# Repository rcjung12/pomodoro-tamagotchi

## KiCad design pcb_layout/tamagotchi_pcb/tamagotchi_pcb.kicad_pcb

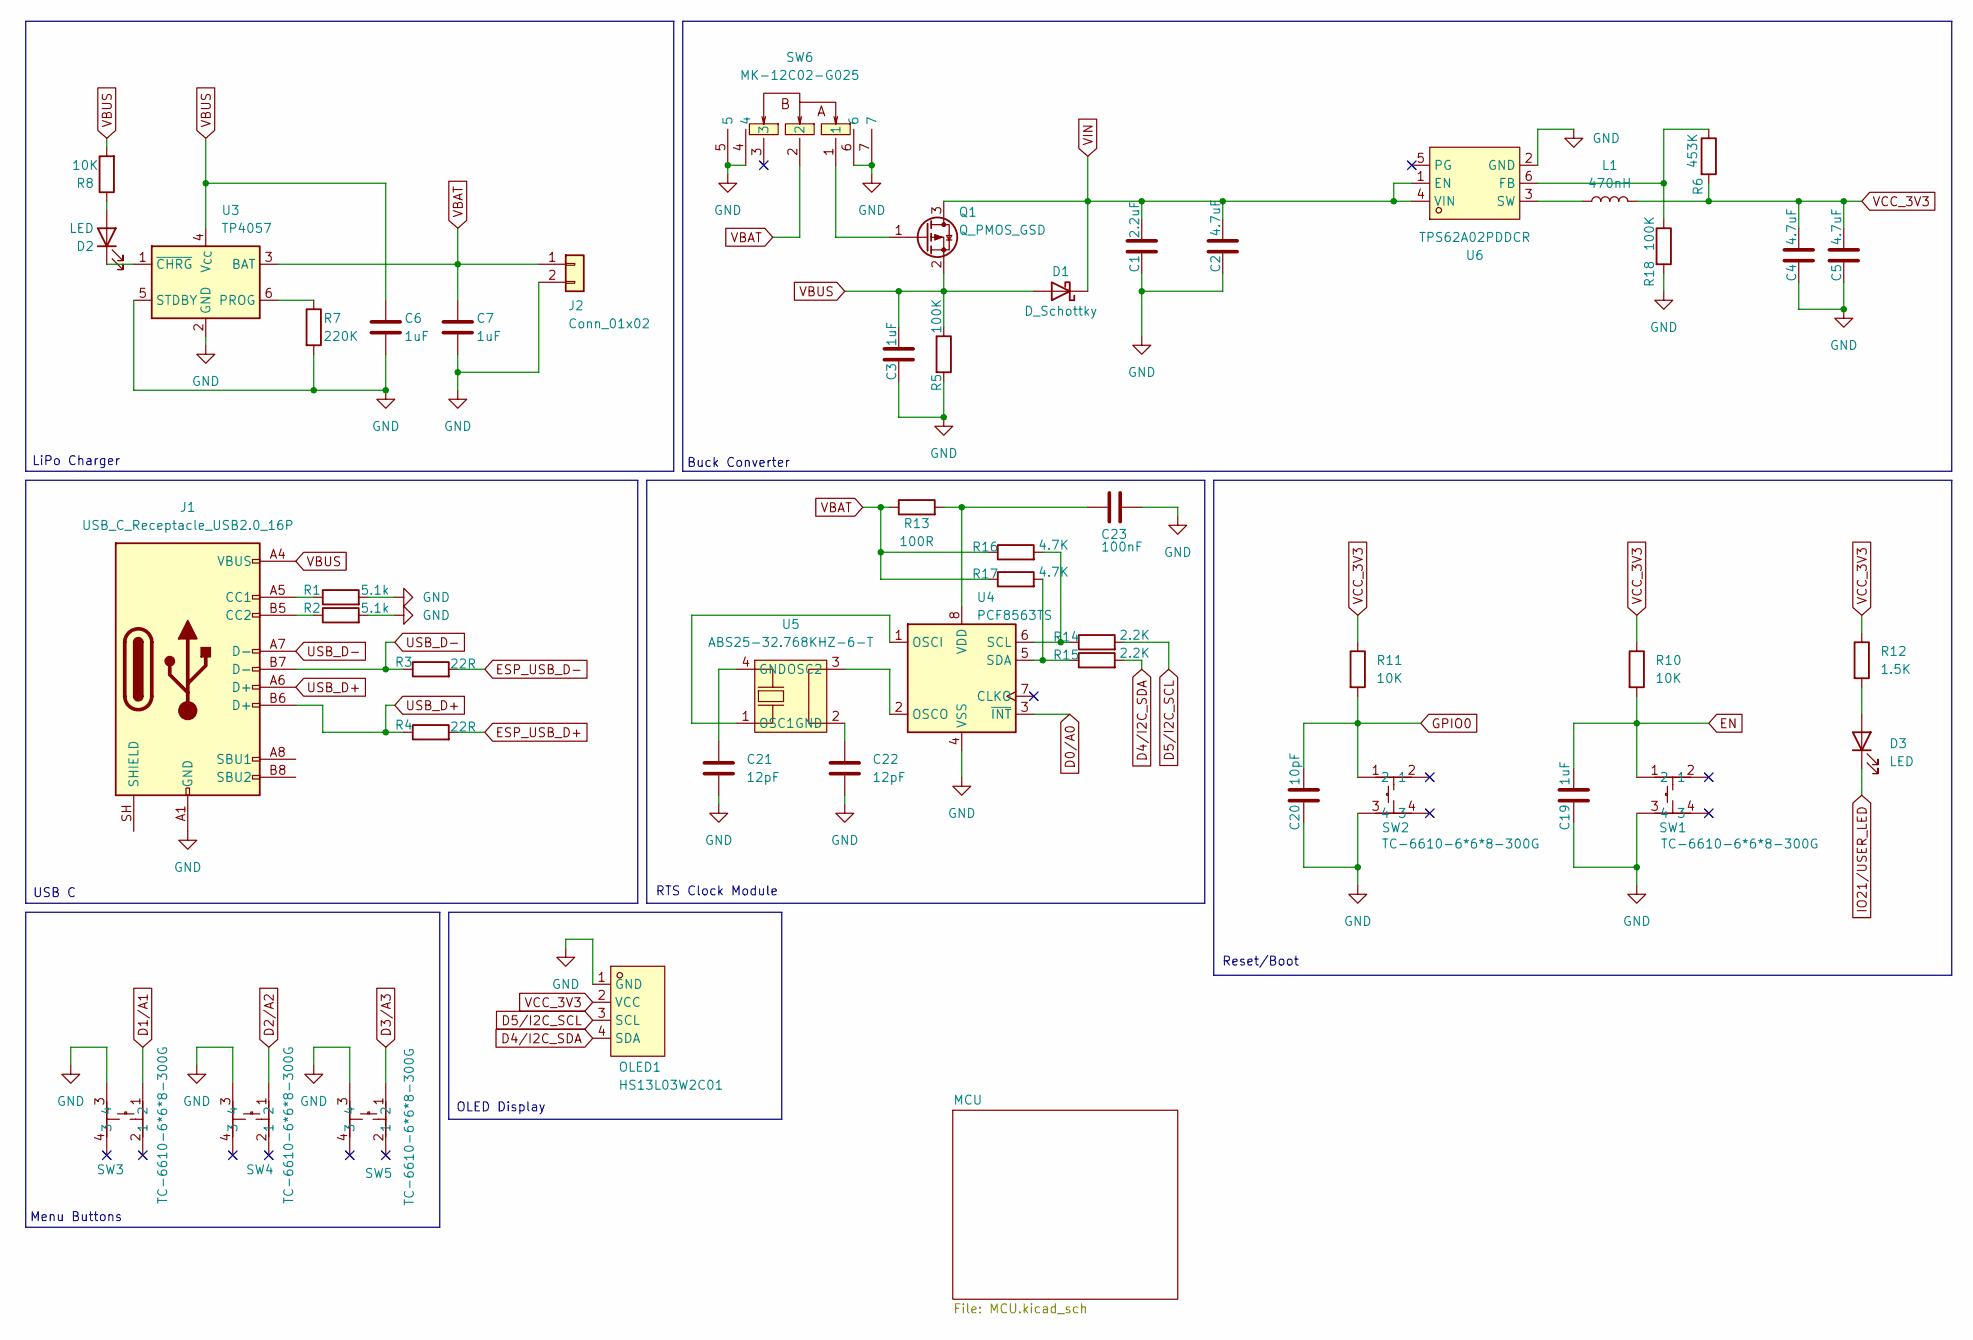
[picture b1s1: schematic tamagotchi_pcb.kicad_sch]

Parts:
C1: 2.2uF; C_0402_1005Metric
C2, C4, C5: 4.7uF; C_0402_1005Metric
C3, C6, C7, C19: 1uF; C_0402_1005Metric
C20: 10pF; C_0402_1005Metric
C21, C22: 12pF; C_0402_1005Metric
C23: 100nF; C_0402_1005Metric
D1: D_Schottky; D_SOD-123
D2, D3: LED; LED_0402_1005Metric
J1: USB_C_Receptacle_USB2.0_16P; USB_C_Receptacle_GCT_USB4105-xx-A_16P_TopMnt_Horizontal
J2: Conn_01x02; JST_PH_S2B-PH-K_1x02_P2.00mm_Horizontal
L1: 470nH; L_0402_1005Metric
OLED1: HS13L03W2C01; OLED-TH_L35.4-W33.5_HS13L03W2C01; MPN HS13L03W2C01; LCSC Part C7465997
Q1: Q_PMOS_GSD; SOT-23
R1, R2: 5.1k; R_0402_1005Metric
R3, R4: 22R; R_0402_1005Metric
R5, R18: 100K; R_0402_1005Metric
R6: 453K; R_0402_1005Metric
R7: 220K; R_0402_1005Metric
R8, R10, R11: 10K; R_0402_1005Metric
R12: 1.5K; R_0402_1005Metric
R13: 100R; R_0402_1005Metric
R14, R15: 2.2K; R_0402_1005Metric
R16, R17: 4.7K; R_0402_1005Metric
SW1, SW2, SW3, SW4, SW5: TC-6610-6*6*8-300G; KEY-TH_4P-L6.0-W6.0-P4.50-LS6.50; MPN TC-6610-6*6*8-300g; LCSC Part C7528712
SW6: MK-12C02-G025; SW-SMD_MK-12C02-G025; MPN MK-12C02-G025; LCSC Part C778186
U3: TP4057; TSOT-23-6
U4: PCF8563TS; MSOP-8_3x3mm_P0.65mm
U5: ABS25-32.768KHZ-6-T; SOJ-4_L8.4-W3.8-P5.5-BL; MPN ABS25-32.768KHZ-6-T; LCSC Part C1985642
U6: TPS62A02PDDCR; SOT-23-6_L2.9-W1.6-P0.95-LS2.9-BL; MPN TPS62A02PDDCR; LCSC Part C22445521

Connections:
D0/A0: U4.3 (~INT); also elsewhere on the board
D1/A1: SW3.1; also elsewhere on the board
D2/A2: SW4.1; also elsewhere on the board
D3/A3: SW5.1; also elsewhere on the board
D4/I2C_SDA: OLED1.4 (SDA), R15.2; also elsewhere on the board
D5/I2C_SCL: OLED1.3 (SCL), R14.2; also elsewhere on the board
EN: C19.1, R10.2, SW1.1; also elsewhere on the board
ESP_USB_D+: R4.2; also elsewhere on the board
ESP_USB_D-: R3.2; also elsewhere on the board
GND: C1.2, C2.2, C3.2, C4.2, C5.2, C6.2, C7.2, C19.2, C20.2, C21.2, C22.2, C23.2, J1.A1 (GND), J1.A12 (GND), J1.B1 (GND), J1.B12 (GND), J2.2, OLED1.1 (GND), R1.2, R2.2, R5.2, R7.2, R18.2, SW1.3, SW2.3, SW3.3, SW4.3, SW5.3, SW6.4, SW6.5, SW6.6, SW6.7, U3.2 (GND), U3.5 (STDBY), U4.4 (VSS), U6.2 (GND); also elsewhere on the board
GPIO0: C20.1, R11.2, SW2.1
IO21/USER_LED: D3.1 (K); also elsewhere on the board
unnamed: C21.1, U5.4 (GND)
unnamed: C22.1, U5.2 (GND)
unnamed: D2.2 (A), R8.1
unnamed: D2.1 (K), U3.1 (~CHRG)
unnamed: D3.2 (A), R12.2
unnamed: J1.A5 (CC1), R1.1
unnamed: J1.B5 (CC2), R2.1
unnamed: Q1.1 (G), SW6.1
unnamed: R7.1, U3.6 (PROG)
unnamed: U4.1 (OSCI), U5.1 (OSC1)
unnamed: U4.2 (OSCO), U5.3 (OSC2)
unnamed: R14.1, R16.2, U4.6 (SCL)
unnamed: R15.1, R17.2, U4.5 (SDA)
unnamed: C23.1, R13.2, U4.8 (VDD)
unnamed: R6.1, R18.1, U6.6 (FB)
unnamed: L1.1, U6.3 (SW)
USB_D+: J1.A6 (D+), J1.B6 (D+), R4.1
USB_D-: J1.A7 (D-), J1.B7 (D-), R3.1
VBAT: C7.1, J2.1, R13.1, R16.1, R17.1, SW6.2, U3.3 (BAT)
VBUS: C3.1, C6.1, D1.2 (A), J1.A4 (VBUS), J1.A9 (VBUS), J1.B4 (VBUS), J1.B9 (VBUS), Q1.2 (S), R5.1, R8.2, U3.4 (V_{CC})
VCC_3V3: C4.1, C5.1, L1.2, OLED1.2 (VCC), R6.2, R10.1, R11.1, R12.1; also elsewhere on the board
VIN: C1.1, C2.1, D1.1 (K), Q1.3 (D), U6.1 (EN), U6.4 (VIN)

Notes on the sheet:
RTS Clock Module
OLED Display
Menu Buttons
Reset/Boot
Buck Converter
USB C
LiPo Charger

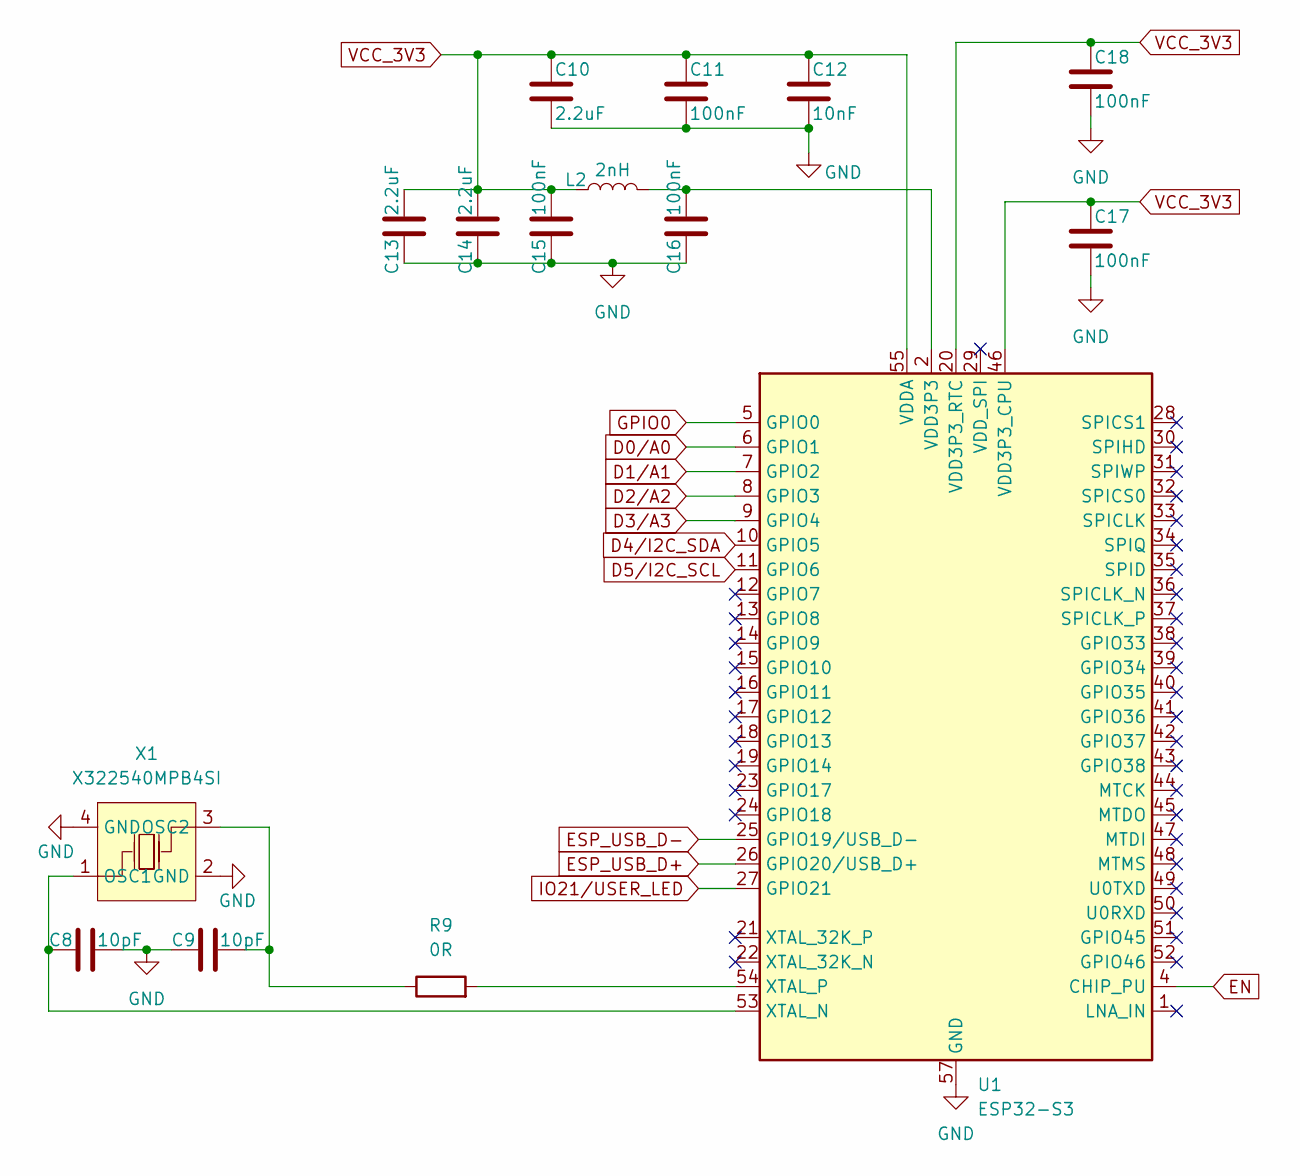
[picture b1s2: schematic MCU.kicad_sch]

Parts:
C8, C9: 10pF; C_0402_1005Metric
C10, C13, C14: 2.2uF; C_0402_1005Metric
C11, C15, C16, C17, C18: 100nF; C_0402_1005Metric
C12: 10nF; C_0402_1005Metric
L2: 2nH; L_0402_1005Metric
R9: 0R; R_0402_1005Metric
U1: ESP32-S3; QFN-56-1EP_7x7mm_P0.4mm_EP4x4mm
X1: X322540MPB4SI; OSC-SMD_4P-L3.2-W2.5-BL_SIT8008BI; MPN X322540MPB4SI; LCSC Part C9010

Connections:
D0/A0: U1.6 (GPIO1); also elsewhere on the board
D1/A1: U1.7 (GPIO2); also elsewhere on the board
D2/A2: U1.8 (GPIO3); also elsewhere on the board
D3/A3: U1.9 (GPIO4); also elsewhere on the board
D4/I2C_SDA: U1.10 (GPIO5); also elsewhere on the board
D5/I2C_SCL: U1.11 (GPIO6); also elsewhere on the board
EN: U1.4 (CHIP_PU); also elsewhere on the board
ESP_USB_D+: U1.26 (GPIO20/USB_D+); also elsewhere on the board
ESP_USB_D-: U1.25 (GPIO19/USB_D-); also elsewhere on the board
GND: C8.2, C9.1, C10.2, C11.2, C12.2, C13.2, C14.2, C15.2, C16.2, C17.2, C18.2, U1.57 (GND), X1.2 (GND), X1.4 (GND); also elsewhere on the board
IO21/USER_LED: U1.27 (GPIO21); also elsewhere on the board
unnamed: C16.1, L2.2, U1.2 (VDD3P3), U1.3 (VDD3P3)
unnamed: C8.1, U1.53 (XTAL_N), X1.1 (OSC1)
unnamed: R9.2, U1.54 (XTAL_P)
unnamed: C9.2, R9.1, X1.3 (OSC2)
VCC_3V3: C10.1, C11.1, C12.1, C13.1, C14.1, C15.1, C17.1, C18.1, L2.1, U1.20 (VDD3P3_RTC), U1.46 (VDD3P3_CPU), U1.55 (VDDA), U1.56 (VDDA); also elsewhere on the board

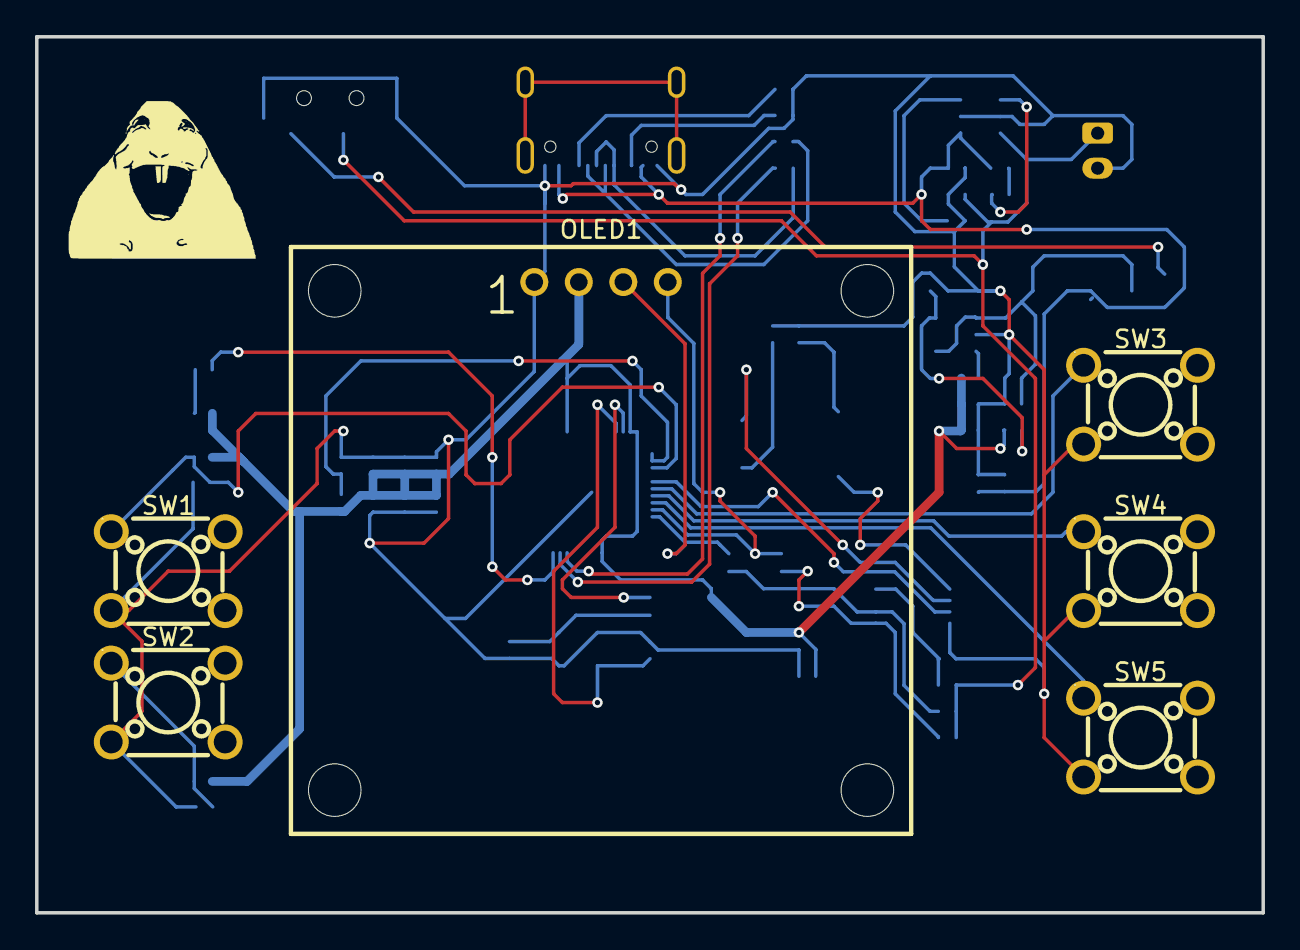
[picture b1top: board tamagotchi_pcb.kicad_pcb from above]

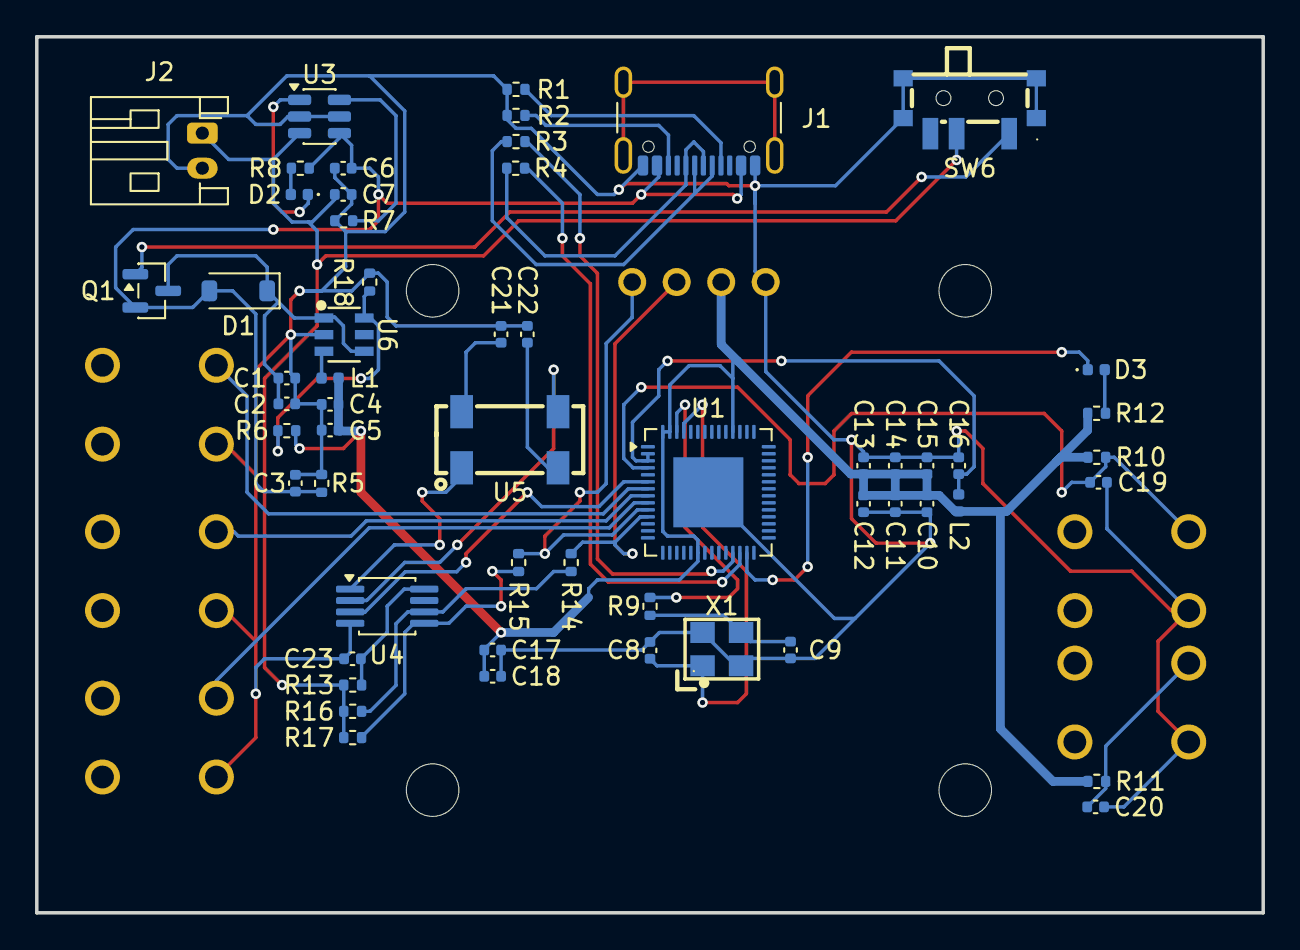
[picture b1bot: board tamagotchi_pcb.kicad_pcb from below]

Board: 2 copper layers, 70.0 x 50.0 mm, 62 parts (56 on the bottom side), 38 nets.

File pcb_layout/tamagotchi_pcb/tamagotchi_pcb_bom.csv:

"Id";"Designator";"Footprint";"Quantity";"Designation";"Supplier and ref";
1;"C1, C10, C13, C14";"C_0402_1005Metric";4;"2.2uF";;;
2;"C2, C4, C5";"C_0402_1005Metric";3;"4.7uF";;;
3;"C3, C6, C7, C19";"C_0402_1005Metric";4;"1uF";;;
4;"C8, C9, C20";"C_0402_1005Metric";3;"10pF";;;
5;"C11, C15, C16, C17, C18, C23";"C_0402_1005Metric";6;"100nF";;;
6;"C12";"C_0402_1005Metric";1;"10nF";;;
7;"C21, C22";"C_0402_1005Metric";2;"12.5pF";;;
8;"D1";"D_SOD-123";1;"D_Schottky";;;
9;"D2, D3";"LED_0402_1005Metric";2;"LED";;;
10;"J1";"USB_C_Receptacle_GCT_USB4105-xx-A_16P_TopMnt_Horizontal";1;"USB_C_Receptacle_USB2.0_16P";;;
11;"J2";"JST_PH_S2B-PH-K_1x02_P2.00mm_Horizontal";1;"Conn_01x02";;;
12;"L1";"L_0402_1005Metric";1;"470nH";;;
13;"L2";"L_0402_1005Metric";1;"2nH";;;
14;"OLED1";"OLED-TH_L35.4-W33.5_HS13L03W2C01";1;"HS13L03W2C01";;;
15;"Q1";"SOT-23";1;"Q_PMOS_GSD";;;
16;"R1, R2";"R_0402_1005Metric";2;"5.1k";;;
17;"R3, R4";"R_0402_1005Metric";2;"22R";;;
18;"R5";"R_0402_1005Metric";1;"100K";;;
19;"R6";"R_0402_1005Metric";1;"249K";;;
20;"R7";"R_0402_1005Metric";1;"220K";;;
21;"R8, R10, R11";"R_0402_1005Metric";3;"10K";;;
22;"R9";"R_0402_1005Metric";1;"0R";;;
23;"R12";"R_0402_1005Metric";1;"1.5K";;;
24;"R13";"R_0402_1005Metric";1;"100R";;;
25;"R14, R15";"R_0402_1005Metric";2;"2.2K";;;
26;"R16, R17";"R_0402_1005Metric";2;"4.7K";;;
27;"SW1, SW2";"KEY-SMD_4P-L2.6-W1.6-P0.80-LS3.0";2;"SKTAAAE010";;;
28;"SW3, SW4, SW5";"KEY-SMD_4P-L4.2-W3.2-P2.20-LS4.6";3;"SKRPACE010";;;
29;"SW6";"SW-SMD_MK-12C02-G025";1;"MK-12C02-G025";;;
30;"U1";"QFN-56-1EP_7x7mm_P0.4mm_EP4x4mm";1;"ESP32-S3";;;
31;"U2";"WLCSP-6_L1.0-W0.7-R2-C3-P0.35-BL";1;"SGM6029CYG/TR";;;
32;"U3";"TSOT-23-6";1;"TP4057";;;
33;"U4";"MSOP-8_3x3mm_P0.65mm";1;"PCF8563TS";;;
34;"U5";"SOJ-4_L8.4-W3.8-P5.5-BL";1;"ABS25-32.768KHZ-6-T";;;
35;"X1";"OSC-SMD_4P-L3.2-W2.5-BL_SIT8008BI";1;"X322540MPB4SI";;;

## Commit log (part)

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2026-03-02 Reorganization
2026-03-02 Add MIT License to the project
2026-03-02 File seperations and project includes file
2026-03-11 feat: simulation package
2026-04-06 fixed animation and reset button
2026-04-13 Created health stats and status bar
2026-04-20 Created eating animation and solved ram shortage
2026-04-20 Added sleep mode
2026-04-21 no message
